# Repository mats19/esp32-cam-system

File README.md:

# ESP32-Cam Autonomous MQTT Camera

## Concept
This circuit realizes an autonomous, battery-powered surveillance camera based on the ESP32-Cam (AI-Thinker model).

### Functionality
* **Autonomous Operation:** Designed for long-term battery use.
* **Interval Capture:** The ESP32 wakes up at defined intervals, captures a photo, and sends it via WiFi/MQTT to a Home Assistant instance.
* **Power Efficiency:** Uses Deep Sleep mode between cycles to minimize power consumption.
* **Manual Trigger:** A tactile button allows manual image triggering at any time.
* **Status Indication:** Two LEDs provide visual feedback for status or errors (e.g., connection issues).

## Project Structure
The repository is organized to separate hardware design from firmware development while maintaining a unified workspace.

```text
esp32-cam-system/           # Root directory (Open this in VS Code)
├── .gitignore              # Global ignore rules for PIO and KiCad
├── platformio.ini          # Central configuration (redirects to firmware/)
├── README.md               # Project documentation
├── .vscode/                # VS Code specific settings
│   ├── settings.json       # IntelliSense and include paths
│   └── tasks.json          # Build and Upload shortcuts
├── firmware/               # Firmware source files
│   └── src/                # .cpp and .h files (Logic & Headers)
├── hardware/               # KiCad PCB project
│   ├── esp32-cam-hw.kicad_pro
│   └── libraries/          # Local Footprints and Symbols
└── docs/                   # Datasheets, 3D models (STL), and images
```

## Development Environment & Settings

### PlatformIO & VS Code
To maintain a clean root directory while keeping firmware in a subfolder, the central `platformio.ini` is configured as follows:
* **Custom Paths:** Redirects `src_dir` and `include_dir` to the `firmware/` folder.
* **Hardware Abstraction:** PSRAM is explicitly enabled via build flags (`-DBOARD_HAS_PSRAM`) to handle image processing.
* **IntelliSense:** The `.vscode/settings.json` includes `${workspaceFolder}/firmware/src` to ensure header files are recognized without errors.

### KiCad Workflow
* **Portability:** All custom footprints and symbols are stored in `hardware/libraries/`.
* **Path Variables:** Library paths should use the `${KIPRJMOD}/libraries/` variable to ensure the project remains functional when cloned to different machines.

## Hardware Description

### Components

#### Main Board
* **U1 (ESP32-Cam AI-Thinker):** Core module containing the ESP32-S SoC, camera, and SD card slot.
* **J1 (Power Supply):** 2-pin JST-XH connector for 5V external power.
* **J2 (Programming):** 5-pin header for FTDI flashing and UART debugging.
* **J3 (Front Panel Link):** 4-pin socket to connect the daughterboard.

#### Daughterboard (Front Panel)
* **SW1 (Button):** Manual capture trigger, push button DTR 7/RT (Connects IO12 to GND).
* **D1 (Red LED):** Error indicator (MQTT/WiFi failure).
* **D2 (Status LED):** Activity indicator (Capturing/Processing).

### Connections and Pinout

| Pin | J2 (Programming) | J3 / J4 (Link) | GPIO | Description |
|---|---|---|---|---|
| 1 | 5V | GND | - | Common Ground |
| 2 | GND | TRIGGER | IO12 | Manual trigger / Wake-up |
| 3 | U0T (TX) | ERR_LED | IO13 | Error LED (Red) |
| 4 | U0R (RX) | STS_LED | IO15 | Status LED |
| 5 | IO0 | - | IO0 | Pull to GND for flashing |

## PCB Milling Specifications (Isolation Milling)
Optimized for CNC isolation milling on copper-clad boards.

### Manufacturing Parameters
* **Track Width:** 0.5 mm to 0.8 mm (Signals); 1.0 mm (Power).
* **Clearance (Isolation Gap):** 0.4 mm to 0.6 mm.
* **THT Pads:** Standard 2.0 mm outer diameter (1.0 mm drill). Custom footprints (e.g. SW1 DTR 7/RT) use 2.6 mm pads with 2.0 mm drills to maintain isolation gaps.
* **Thermal Reliefs:** Required for all pads in copper zones.
* **Antenna Cutout:** Instead of a standard keepout zone, a rectangle is drawn on the `User.Drawings` layer. This area under the ESP32-S PCB antenna will be completely milled out (freigefräst) to avoid WiFi signal attenuation.

### Milling Constraints
* **Tooling:** 30° Engraving Bit.
* **Depth of Cut:** 0.05 mm to 0.1 mm (Auto-leveling highly recommended).

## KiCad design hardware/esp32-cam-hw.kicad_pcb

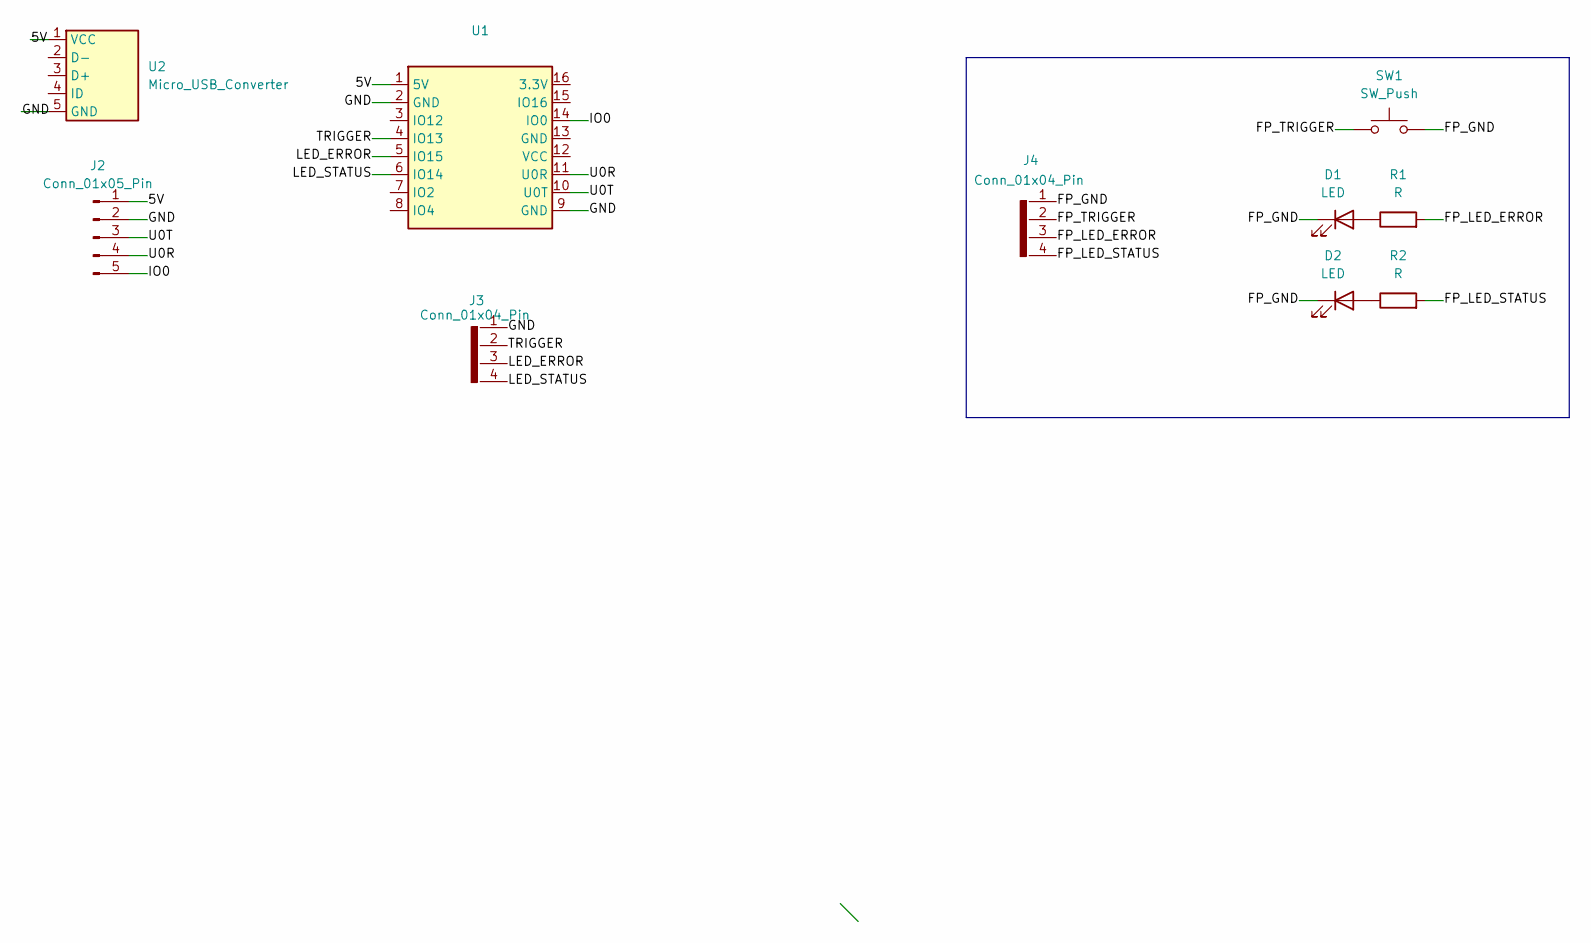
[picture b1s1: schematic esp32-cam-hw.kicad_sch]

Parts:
D1, D2: LED; LED_D5.0mm
J2: Conn_01x05_Pin; JST_EH_S5B-EH_1x05_P2.50mm_Horizontal
J3, J4: Conn_01x04_Pin; PinHeader_1x04_P2.54mm_Vertical
R1, R2: R; R_Axial_DIN0207_L6.3mm_D2.5mm_P7.62mm_Horizontal
SW1: SW_Push; SW_DTR_7_RT
U1: ESP32-Cam AI-Thinker Model
U2: Micro_USB_Converter

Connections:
/5V: J2.1, U1.1 (5V), U2.1 (VCC)
/FP_GND: D1.1 (K), D2.1 (K), J4.1, SW1.2
/FP_LED_ERROR: J4.3, R1.2
/FP_LED_STATUS: J4.4, R2.2
/FP_TRIGGER: J4.2, SW1.1
/GND: J2.2, J3.1, U1.2 (GND), U1.9 (GND), U2.5 (GND)
/IO0: J2.5, U1.14 (IO0)
/LED_ERROR: J3.3, U1.5 (IO15)
/LED_STATUS: J3.4, U1.6 (IO14)
/TRIGGER: J3.2, U1.4 (IO13)
/U0R: J2.4, U1.11 (U0R)
/U0T: J2.3, U1.10 (U0T)
unnamed: D1.2 (A), R1.1
unnamed: D2.2 (A), R2.1

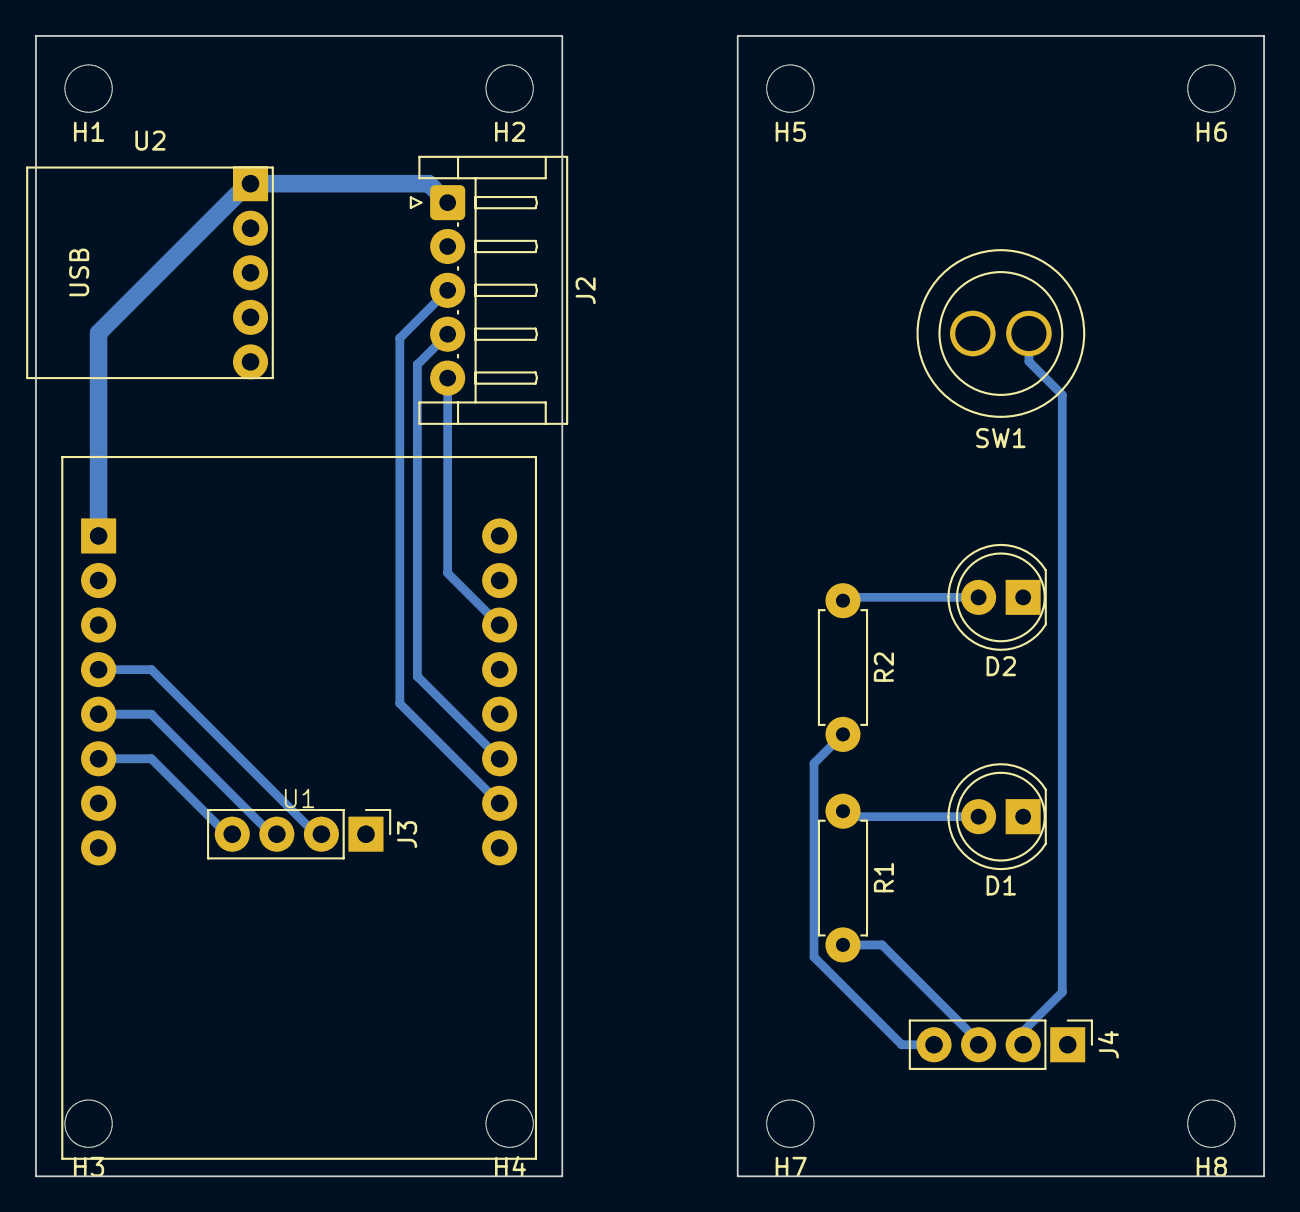
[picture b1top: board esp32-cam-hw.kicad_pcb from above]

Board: 2 copper layers, 70.0 x 65.0 mm, 18 parts (0 on the bottom side), 14 nets.

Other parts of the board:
H1, H2, H3, H4, H5, H6, H7, H8: MountingHole_2.7mm_M2.5

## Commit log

2026-03-18 Migration inkl. Libraries abgeschlossen
2026-03-18 Initial migration: restructured ESP32-CAM project
2026-03-18 Fix: converted firmware submodule to regular folder
2026-03-18 Add project documentation
2026-03-18 Clean up: removed redundant gitignore in firmware folder
2026-03-18 Apply optimized global gitignore
2026-03-18 Restructured project: Unified PlatformIO and KiCad root, optimized .gitignore, and configured VS Code tasks
2026-03-18 docs: Translate README to English and expand project documentation
    - Translated the core concept and hardware descriptions from German to English.
    - Added a detailed project directory structure tree.
    - Formatted hardware components and connections into clear lists and tables.
    - Included PlatformIO and KiCad development environment settings.
    - Added CNC isolation milling specifications and constraints for the PCB.
2026-03-19 Hardware: Center front panel components and add custom switch footprint
    - Centered front panel components (SW1, D1, D2, J3, J4) precisely on the X-axis for optical symmetry.
    - Added a custom KiCad footprint for the DTR 7/RT push button (9.5mm body, round).
    - Adjusted THT pad sizes for the custom switch (2.6mm outer diameter, 2.0mm drill) to guarantee a minimum 0.6mm gap for CNC isolation milling.
    - Updated README.md to reflect the specific switch model and adjusted PCB milling specifications.
2026-03-19 Hardware: Replace antenna keepout zone with milling rectangle
    - Removed the standard KiCad keepout zone under the ESP32-S antenna.
    - Added a filled rectangle on the `Dwgs.User` (User.Drawings) layer to serve as a precise milling pocket for CNC isolation routing.
    - Adjusted the GND copper polygon to perfectly avoid the antenna region.
    - Updated README.md to document the new antenna cutout milling procedure.
